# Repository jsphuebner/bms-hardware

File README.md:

# bms-hardware
Hardware design files for Lithium BMS

# License
Attribution-ShareAlike 4.0 International
https://creativecommons.org/licenses/by-sa/4.0/legalcode

You musn't change the copyright info (J. Huebner/A. Martell and openinverter.org) on the silkscreen in size location or content.

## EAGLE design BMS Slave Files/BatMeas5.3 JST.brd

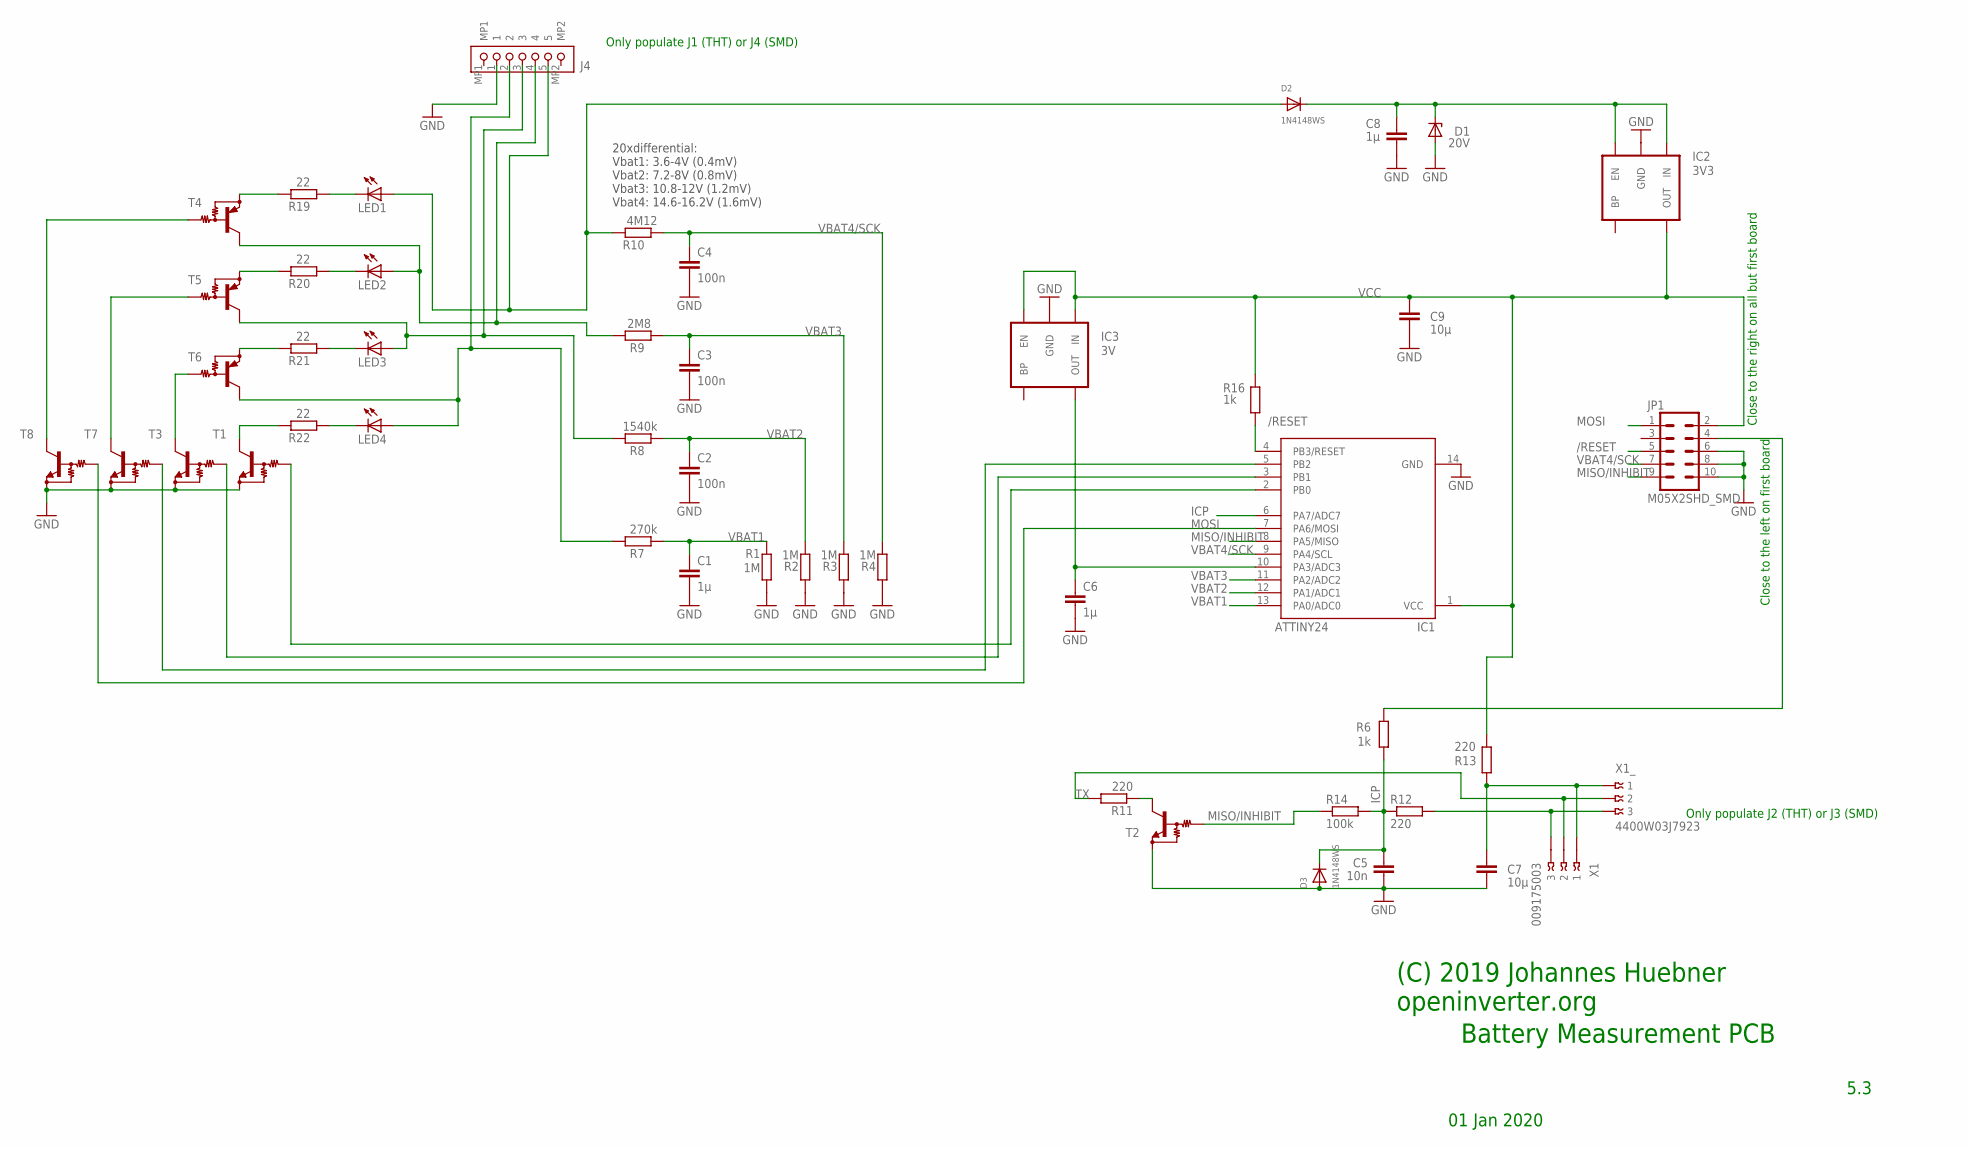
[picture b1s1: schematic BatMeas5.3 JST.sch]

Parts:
C1, C6: 1µ; C0603
C2, C3, C4: 100n; C0603
C5: 10n; C0603
C7, C9: 10µ; C0805
C8: 1µ; C0805
D1: 20V; SMB
D2, D3: 1N4148WS; SOD-323F
IC1: ATTINY24; SO014
IC2: 3V3; SOT23-5
IC3: 3V; SOT23-5
J4: BM05B-PASS-1-TFT_(LF)(SN)SMD; BM05BPASS1TFTLFSN
JP1: M05X2SHD_SMD; 2X5-SHROUDED_SMD
LED1, LED2, LED3, LED4: 150060GS75000; CHIPLED_0805
R1, R2, R3, R4: 1M; R0603
R6, R16: 1k; R0603
R7: 270k; R0603
R8: 1540k; R0603
R9: 2M8; R0603
R10: 4M12; R0603
R11, R12, R13: 220; R0603
R14: 100k; R0603
R19, R20, R21, R22: 22; R0805
T1, T2, T3, T7, T8: MMUN2233; SC59-BEC
T4, T5, T6: MMUN2111LT1G; SC59-BEC
X1: 009175003
X1_: 4400W03J7923; 4400WXXJ7923

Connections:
/RESET: IC1.4 (PB3/RESET), JP1.5, R16.2
GND: C1.2, C2.2, C3.2, C4.2, C5.2, C6.2, C7.2, C8.2, C9.2, D1.A, D3.A, IC1.14 (GND), IC2.2 (GND), IC3.2 (GND), J4.1, JP1.6, JP1.8, JP1.10, R1.2, R2.2, R3.2, R4.2, T1.E, T2.E, T3.E, T7.E, T8.E
ICP: C5.1, D3.C, IC1.6 (PA7/ADC7), R6.1, R12.1, R14.2
MISO/INHIBIT: IC1.8 (PA5/MISO), JP1.9, R14.1, T2.B
MOSI: IC1.7 (PA6/MOSI), JP1.1, T8.B
unnamed: T3.C, T6.B
unnamed: C6.1, IC1.10 (PA3/ADC3), IC3.5 (OUT)
unnamed: IC1.2 (PB0), T1.B
unnamed: IC1.3 (PB1), T3.B
unnamed: R19.2, T4.E
unnamed: LED1.C, R19.1
unnamed: JP1.4, R6.2
unnamed: IC1.5 (PB2), T7.B
unnamed: R20.2, T5.E
unnamed: C7.1, R13.2, X1.1@1 (1), X1_.P$1 (1)
unnamed: LED2.C, R20.1
unnamed: R11.1, T2.C
unnamed: D2.A, J4.5, LED1.A, R10.2
unnamed: LED3.C, R21.1
unnamed: LED4.C, R22.1
unnamed: R21.2, T6.E
unnamed: R22.2, T1.C
unnamed: R12.2, X1.3@2 (3), X1_.P$3 (3)
unnamed: J4.4, LED2.A, R9.2, T4.C
unnamed: J4.3, LED3.A, R8.2, T5.C
unnamed: J4.2, LED4.A, R7.2, T6.C
unnamed: T5.B, T7.C
unnamed: T4.B, T8.C
TX: R11.2, X1.2@1 (2), X1_.P$2 (2)
VBAT: C8.1, D1.C, D2.C, IC2.1 (IN), IC2.3 (EN)
VBAT1: C1.1, IC1.13 (PA0/ADC0), R1.1, R7.1
VBAT2: C2.1, IC1.12 (PA1/ADC1), R2.1, R8.1
VBAT3: C3.1, IC1.11 (PA2/ADC2), R3.1, R9.1
VBAT4/SCK: C4.1, IC1.9 (PA4/SCL), JP1.7, R4.1, R10.1
VCC: C9.1, IC1.1 (VCC), IC2.5 (OUT), IC3.1 (IN), IC3.3 (EN), JP1.2, R13.1, R16.1

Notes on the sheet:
20xdifferential: Vbat1: 3.6-4V (0.4mV) Vbat2: 7.2-8V (0.8mV) Vbat3: 10.8-12V (1.2mV) Vbat4: 14.6-16.2V (1.6mV)
Close to the right on all but first board
5.3
(C) 2019 Johannes Huebner openinverter.org
Battery Measurement PCB
01 Jan 2020
Only populate J2 (THT) or J3 (SMD)
Only populate J1 (THT) or J4 (SMD)
Close to the left on first board

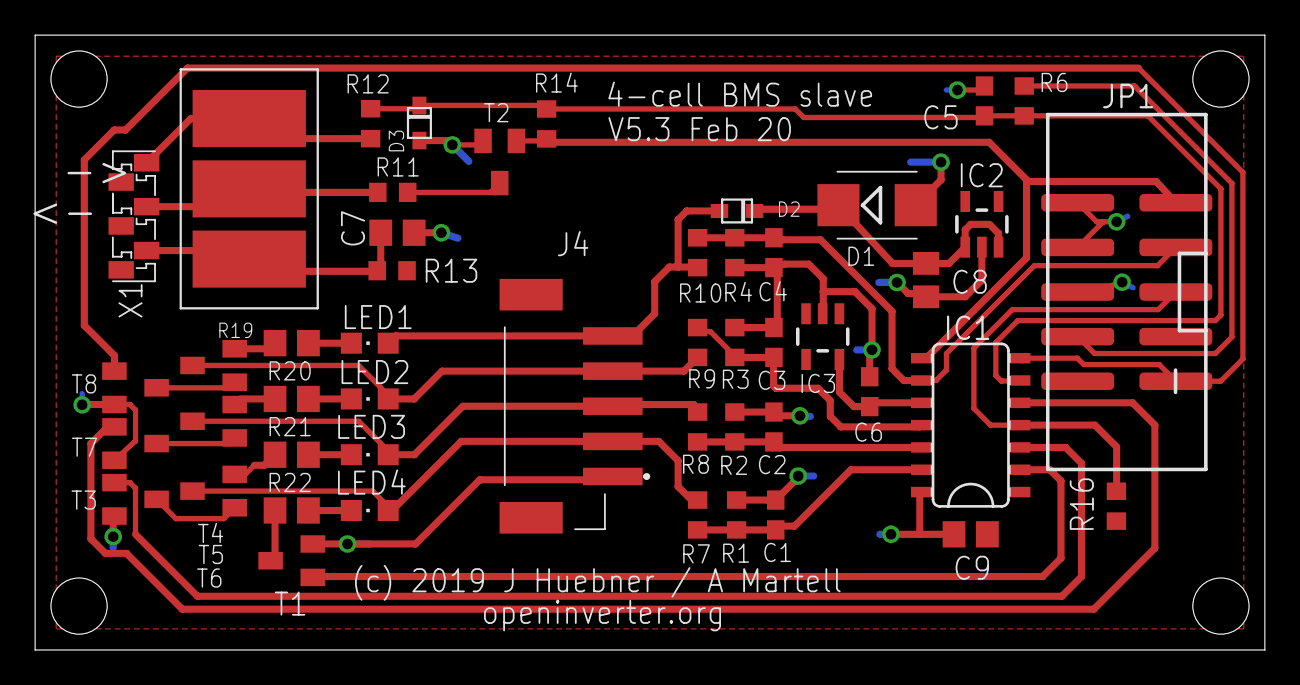
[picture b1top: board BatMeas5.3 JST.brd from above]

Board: 2 copper layers, 70.0 x 35.0 mm, 49 parts (0 on the bottom side), 35 nets.

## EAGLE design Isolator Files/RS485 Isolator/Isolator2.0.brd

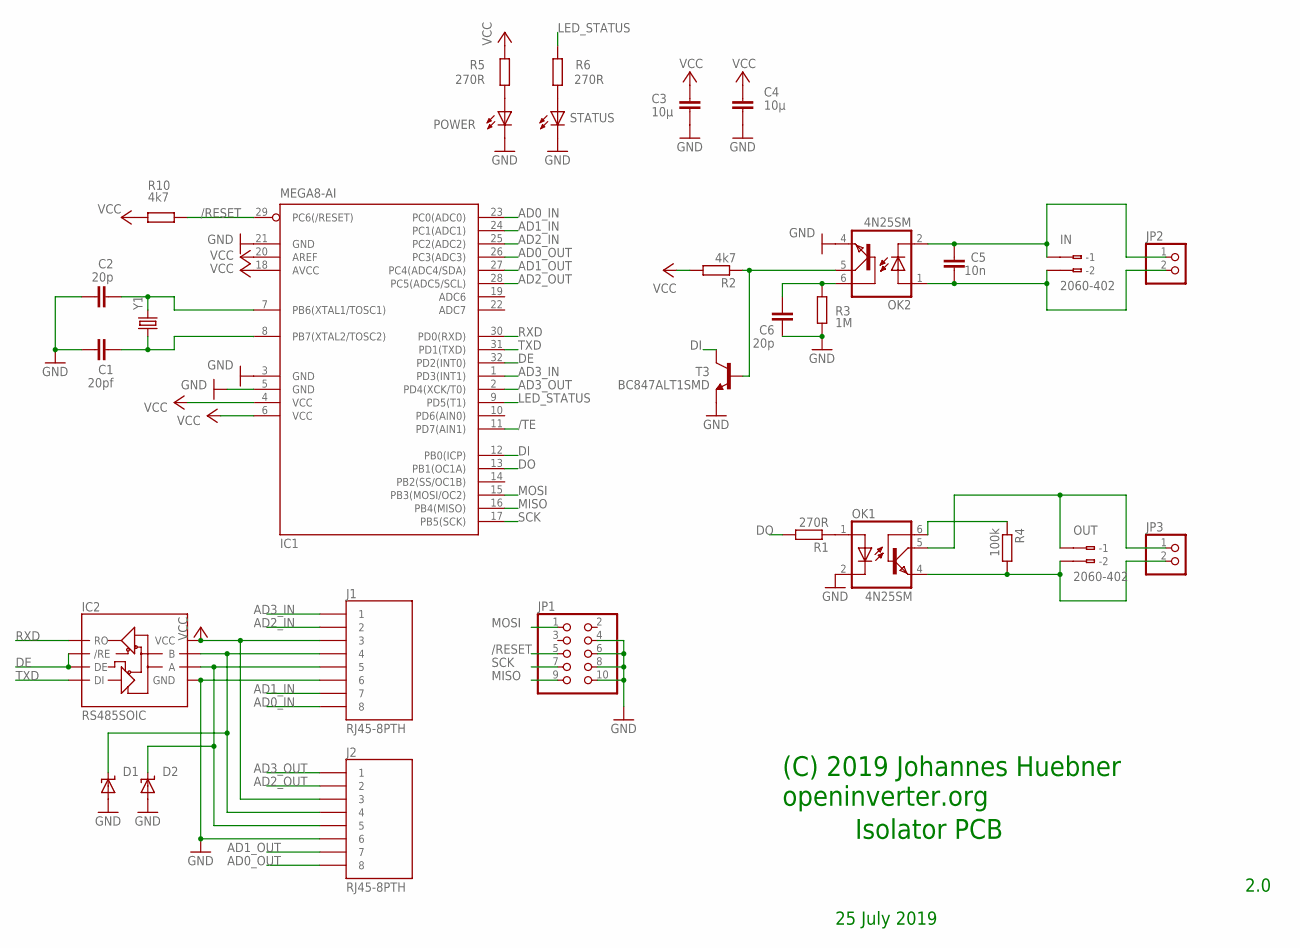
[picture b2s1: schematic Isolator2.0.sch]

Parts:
C1: 20pf; C0805
C2, C6: 20p; C0805
C3, C4: 10µ; C0805
C5: 10n; C0805
D1, D2: SUPPRESSOR-SMBJ; SMBJ
IC1: MEGA8-AI; TQFP32-08
IC2: RS485SOIC; SO08
IN: 2060-402
J1, J2: RJ45-8PTH; RJ45-8
JP1: PINHD-2X5; 2X05
JP2, JP3: PINHD-1X2; 1X02
OK1, OK2: 4N25SM; DIL6-SMD
OUT: 2060-402
POWER: LEDCHIP-LED0805; CHIP-LED0805
R1, R5, R6: 270R; M0805
R2, R10: 4k7; M0805
R3: 1M; M0805
R4: 100k; M0805
STATUS: LEDCHIP-LED0805; CHIP-LED0805
T3: BC847ALT1SMD; SOT23
Y1: CRYSTAL10.5X4.8; CRYSTAL-SMD-10.5X4.8-2PIN

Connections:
/RESET: IC1.29 (PC6(/RESET)), JP1.5, R10.2
/TE: IC1.11 (PD7(AIN1))
AD0_IN: IC1.23 (PC0(ADC0)), J1.8
AD0_OUT: IC1.26 (PC3(ADC3)), J2.8
AD1_IN: IC1.24 (PC1(ADC1)), J1.7
AD1_OUT: IC1.27 (PC4(ADC4/SDA)), J2.7
AD2_IN: IC1.25 (PC2(ADC2)), J1.2
AD2_OUT: IC1.28 (PC5(ADC5/SCL)), J2.2
AD3_IN: IC1.1 (PD3(INT1)), J1.1
AD3_OUT: IC1.2 (PD4(XCK/T0)), J2.1
DE: IC1.32 (PD2(INT0)), IC2.2 (/RE), IC2.3 (DE)
DI: IC1.12 (PB0(ICP)), T3.3 (C)
DO: IC1.13 (PB1(OC1A)), R1.2
GND: C1.1, C2.1, C3.2, C4.2, C6.1, D1.A, D2.A, IC1.3 (GND), IC1.5 (GND), IC1.21 (GND), IC2.5 (GND), J1.6, J2.6, JP1.4, JP1.6, JP1.8, JP1.10, OK1.2 (C), OK2.4 (EMI), POWER.C, R3.2, STATUS.C, T3.2 (E)
LED_STATUS: IC1.9 (PD5(T1)), R6.2
MISO: IC1.16 (PB4(MISO)), JP1.9
MOSI: IC1.15 (PB3(MOSI/OC2)), JP1.1
unnamed: OK1.1 (A), R1.1
unnamed: C6.2, OK2.6 (BAS), R3.1
unnamed: OK2.5 (COL), R2.1, T3.1 (B)
unnamed: OK1.6 (BAS), R4.1
unnamed: D1.C, IC2.7 (B), J1.4, J2.4
unnamed: JP3.2, OK1.4 (EMI), OUT.P22 (B-2), R4.2
unnamed: D2.C, IC2.6 (A), J1.5, J2.5
unnamed: POWER.A, R5.1
unnamed: R6.1, STATUS.A
unnamed: C2.2, IC1.7 (PB6(XTAL1/TOSC1)), Y1.P$2 (2)
unnamed: C1.2, IC1.8 (PB7(XTAL2/TOSC2)), Y1.P$1 (1)
unnamed: C5.1, IN.P22 (B-2), JP2.2, OK2.1 (A)
unnamed: C5.2, IN.P21 (B-1), JP2.1, OK2.2 (C)
unnamed: JP3.1, OK1.5 (COL), OUT.P21 (B-1)
RXD: IC1.30 (PD0(RXD)), IC2.1 (RO)
SCK: IC1.17 (PB5(SCK)), JP1.7
TXD: IC1.31 (PD1(TXD)), IC2.4 (DI)
VCC: C3.1, C4.1, IC1.4 (VCC), IC1.6 (VCC), IC1.18 (AVCC), IC1.20 (AREF), IC2.8 (VCC), J1.3, J2.3, R2.2, R5.2, R10.1

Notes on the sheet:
(C) 2019 Johannes Huebner openinverter.org
Isolator PCB
2.0
25 July 2019

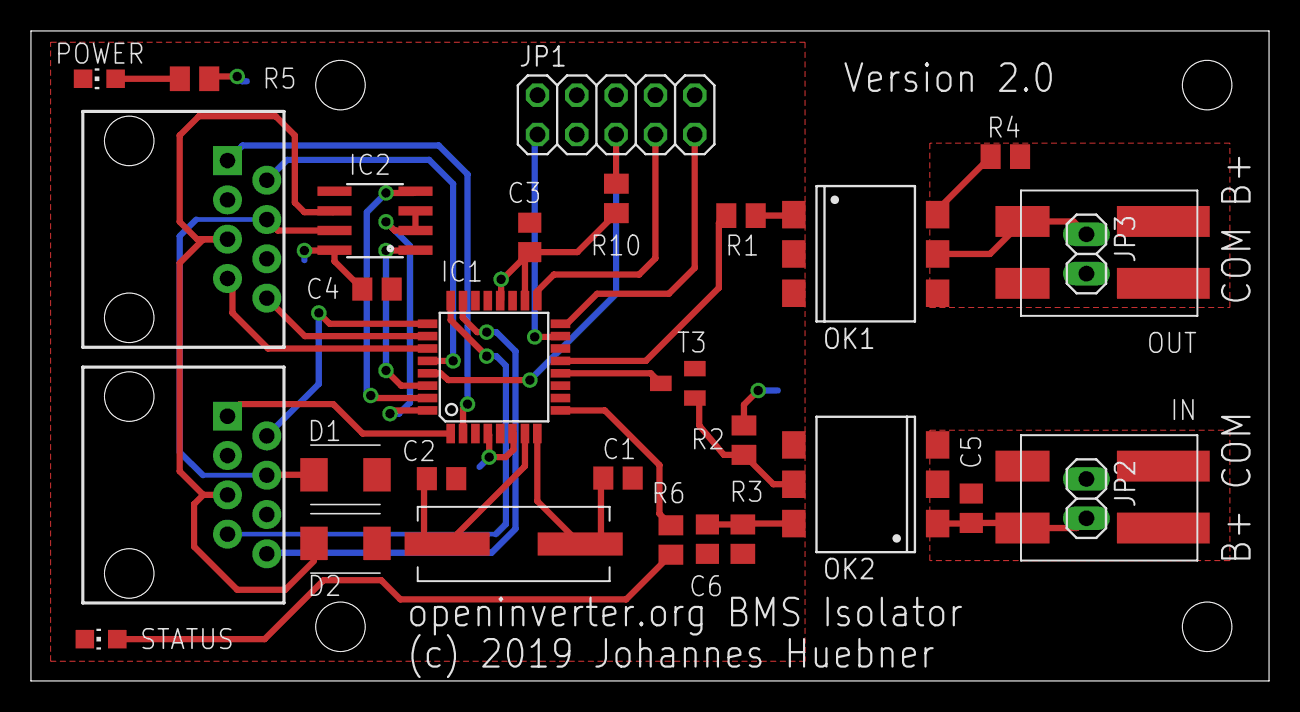
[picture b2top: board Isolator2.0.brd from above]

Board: 2 copper layers, 80.0 x 42.0 mm, 30 parts (0 on the bottom side), 34 nets.

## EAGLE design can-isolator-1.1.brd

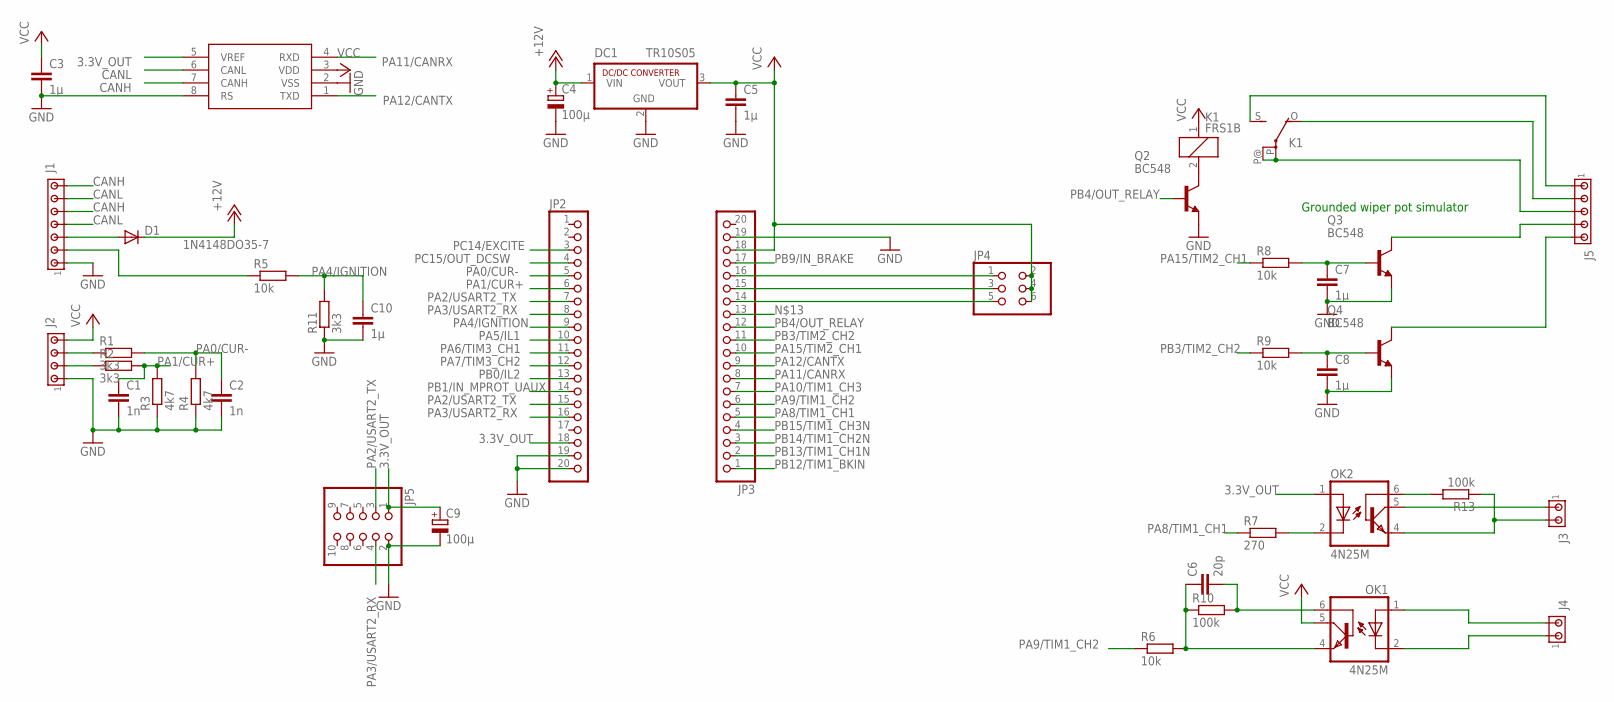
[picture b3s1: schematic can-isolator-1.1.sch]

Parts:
C1, C2: 1n; C025-024X044
C3, C5, C7, C8, C10: 1µ; C025-024X044
C4, C9: 100µ; E2-5
C6: 20p; C025-024X044
D1: 1N4148DO35-7; DO35-7
DC1: TR10S05; SIP3
IC1: MCP2562P; DIL08
J1: MTA07-100; 10X07MTA
J2: MTA04-100; 10X04MTA
J3, J4: MTA02-100; 10X02MTA
J5: MTA05-100; 10X05MTA
JP2, JP3: PINHD-1X20; 1X20
JP4: PINHD-2X3; 2X03
JP5: PINHD-2X5/90; 2X05/90
K1: FRS1B
OK1, OK2: 4N25M; DIL06
Q2, Q3, Q4: BC548; TO92-EBC
R1, R2, R11: 3k3; 0207/10
R3, R4: 4k7; 0207/10
R5, R6, R8, R9: 10k; 0207/10
R7: 270; 0207/10
R10, R13: 100k; 0207/10

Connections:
3.3V_OUT: C9.+, IC1.5 (VREF), JP2.18, JP5.1, OK2.1 (A)
+12V: C4.+, D1.C, DC1.1 (VIN)
CANH: IC1.7 (CANH), J1.5, J1.7
CANL: IC1.6 (CANL), J1.4, J1.6
GND: C1.2, C2.2, C3.2, C4.-, C5.2, C7.2, C8.2, C9.-, C10.2, DC1.2 (GND), IC1.2 (VSS), IC1.8 (RS), J1.1, J2.1, JP2.19, JP2.20, JP3.19, JP5.2, Q2.E, Q3.E, Q4.E, R3.1, R4.1, R11.1
IGNITION: J1.2, R5.1
unnamed: C7.1, Q3.B, R8.2
unnamed: J5.4, Q3.C
unnamed: C8.1, Q4.B, R9.2
unnamed: J5.5, Q4.C
unnamed: K1.2, Q2.C
unnamed: J5.3, K1.P, K1.P@
unnamed: J5.2, K1.O
unnamed: J5.1, K1.S
unnamed: OK2.2 (C), R7.2
unnamed: OK2.6 (BAS), R13.2
unnamed: J3.2, OK2.4 (EMI), R13.1
unnamed: J3.1, OK2.5 (COL)
unnamed: J4.2, OK1.1 (A)
unnamed: J4.1, OK1.2 (C)
unnamed: C6.2, OK1.6 (BAS), R10.2
unnamed: C6.1, OK1.4 (EMI), R6.2, R10.1
unnamed: JP3.14, JP4.5
unnamed: JP3.15, JP4.3
unnamed: JP3.16, JP4.1
unnamed: J2.3, R1.1
unnamed: J2.2, R2.1
unnamed: D1.A, J1.3
PA0/CUR-: C2.1, JP2.5, R1.2, R4.2
PA1/CUR+: C1.1, JP2.6, R2.2, R3.2
PA2/USART2_TX: JP2.7, JP2.15, JP5.3
PA3/USART2_RX: JP2.8, JP2.16, JP5.4
PA4/IGNITION: C10.1, JP2.9, R5.2, R11.2
PA5/IL1: JP2.10
PA6/TIM3_CH1: JP2.11
PA7/TIM3_CH2: JP2.12
PA8/TIM1_CH1: JP3.5, R7.1
PA9/TIM1_CH2: JP3.6, R6.1
PA10/TIM1_CH3: JP3.7
PA11/CANRX: IC1.4 (RXD), JP3.8
PA12/CANTX: IC1.1 (TXD), JP3.9
PA15/TIM2_CH1: JP3.10, R8.1
PB0/IL2: JP2.13
PB1/IN_MPROT_UAUX: JP2.14
PB3/TIM2_CH2: JP3.11, R9.1
PB4/OUT_RELAY: JP3.12, Q2.B
PB9/IN_BRAKE: JP3.17
PB12/TIM1_BKIN: JP3.1
PB13/TIM1_CH1N: JP3.2
PB14/TIM1_CH2N: JP3.3
PB15/TIM1_CH3N: JP3.4
PC14/EXCITE: JP2.3
PC15/OUT_DCSW: JP2.4
VCC: C3.1, C5.1, DC1.3 (VOUT), IC1.3 (VDD), J2.4, JP3.18, JP4.2, JP4.4, JP4.6, K1.1, OK1.5 (COL)

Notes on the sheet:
Grounded wiper pot simulator

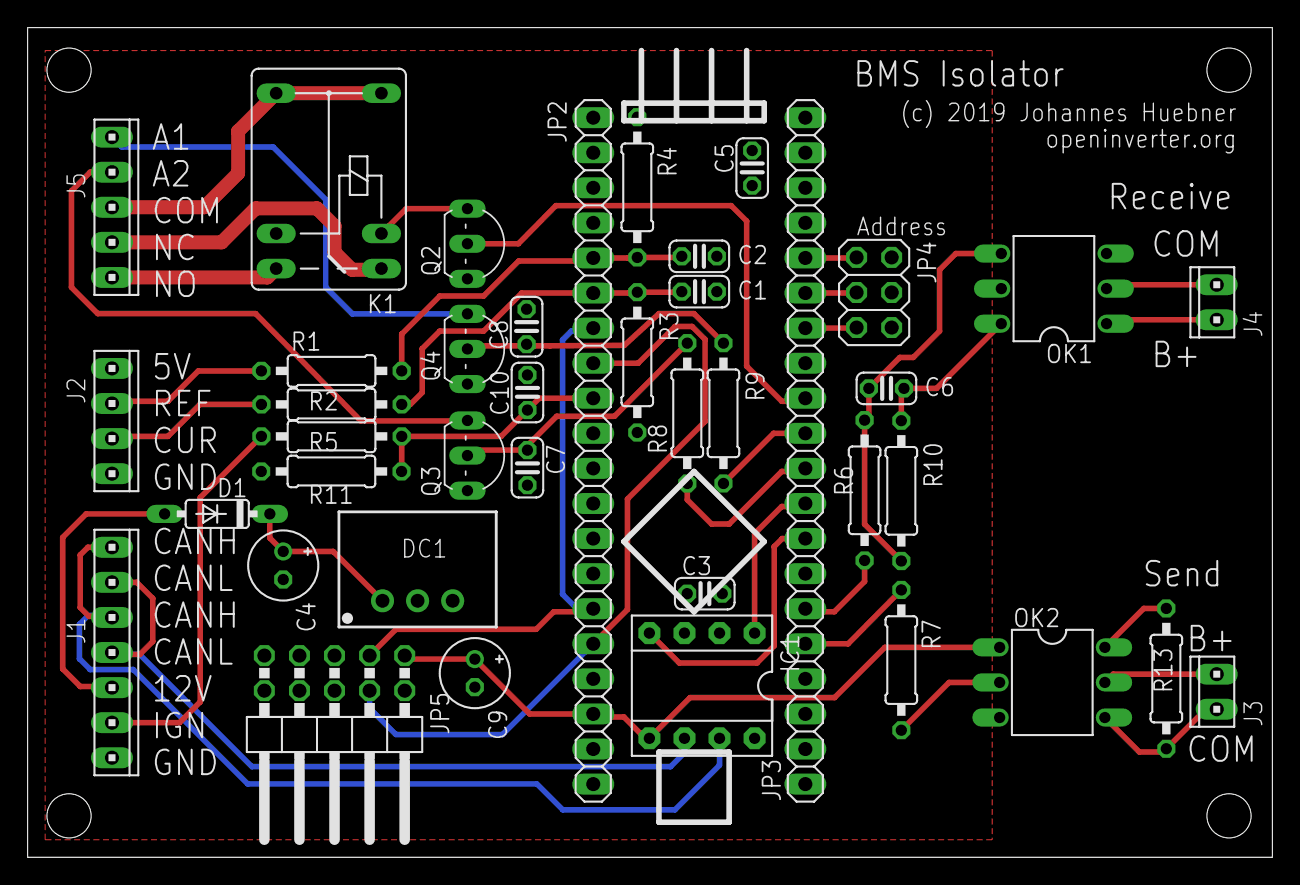
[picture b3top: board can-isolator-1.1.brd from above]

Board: 2 copper layers, 90.1 x 60.1 mm, 40 parts (0 on the bottom side), 41 nets.

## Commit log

2019-07-11 Changed comments and part numbers
2019-07-11 Fixed dangling pin of R6
2019-07-11 Update BatMeas5.1.csv
    Updated IC3 to AP2139AK-3.0TRG1 as ground current is less. Feels more important than a few pennys on cost
2019-07-17 Created version 5.2 with dual connector population
2019-07-18 Enlarged board to space new connectors
    Enlarged board, now 35x70mm. Moved bottom tracks other than ground plane to top side. Holes spaced 2.5mm in from edge of PCB (was 2.54mm)
2019-07-21 Minor updates and added maunfacturing files
2019-07-21 Added zip version of man files
2019-07-22 Updated Isolator board and added manufacturing files
2019-08-16 Added Isolator2.0 BOM
    Added Isolator BOM
2019-08-26 Update BatMeas5.2 Manufacturing BOM.csv
    Changed bleed resistors to 27R, specified voltage divider resistors as 1% tolerance
2019-10-29 Isolator BOM Update
    Added manufacturer details. Updated crystal to 11.0592MHz and changed microcontroller to Atmega88P
2019-12-12 Removed Zener
2020-01-02 Updated slave board: - Populate SMT programming header (also used for calibration) - select 1st board via jumper on programming header - B+ exports 3V3 instead of pack voltage -> no Zener needed. Res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
2020-01-02 Added CAN isolator schematic and layout
2020-01-05 Minor CAN isolator PCB mods to improve track clearance. Added manufacturing data
2020-02-05 Changed C5 to 10n
2020-02-24 Replaced JST comms connector by AVX or 4mm IDC wire to board connector Removed all THT options Removed holes below cell JST connector, made pads longer
2020-02-24 Updated BOM
2020-03-01 Add BOM for Blue Pill CAN Isolator
    Create and add BOM for Blue Pill version of CAN Isolator
2020-03-01 Tidy up file structure
2020-03-01 Added SMT version of CAN isolator
2020-03-02 Added manufacturing files
2020-03-02 Changed value of C6 to 1u
2020-03-02 Added JLCPCB placement and BOM files
2020-05-02 Use Attiny44
2020-05-02 Use 3V3 reg with enable pin
2020-05-02 Move vias further away from opposite pin
2020-05-03 Add CAN Isolator V2 files
    CAN Isolator V2 created. Uses Cinch enclosure.
2020-08-06 Replaced 4M12/1M divider by 3M9/953k divider to stay in JLCPCBs part lib
2020-08-06 Update BOM and placement file after ordering
2020-10-31 Changed R6 from 1k to 4k7, C5 from 10n to 1n, R14 from 100k to 47k
2021-05-05 BOM update

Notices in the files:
BMS Slave Files/BatMeas5.3 JST.brd:
(c) 2019 J Huebner / A Martell
parts and their libraries:
SparkFun-PowerIC: Licensing: CC v3.0 Share-Alike You are welcome to use this library for commercial purposes.
